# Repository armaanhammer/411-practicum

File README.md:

# 411-practicum
Development for ECE 411 Fall 2017 Group 16 Practicum

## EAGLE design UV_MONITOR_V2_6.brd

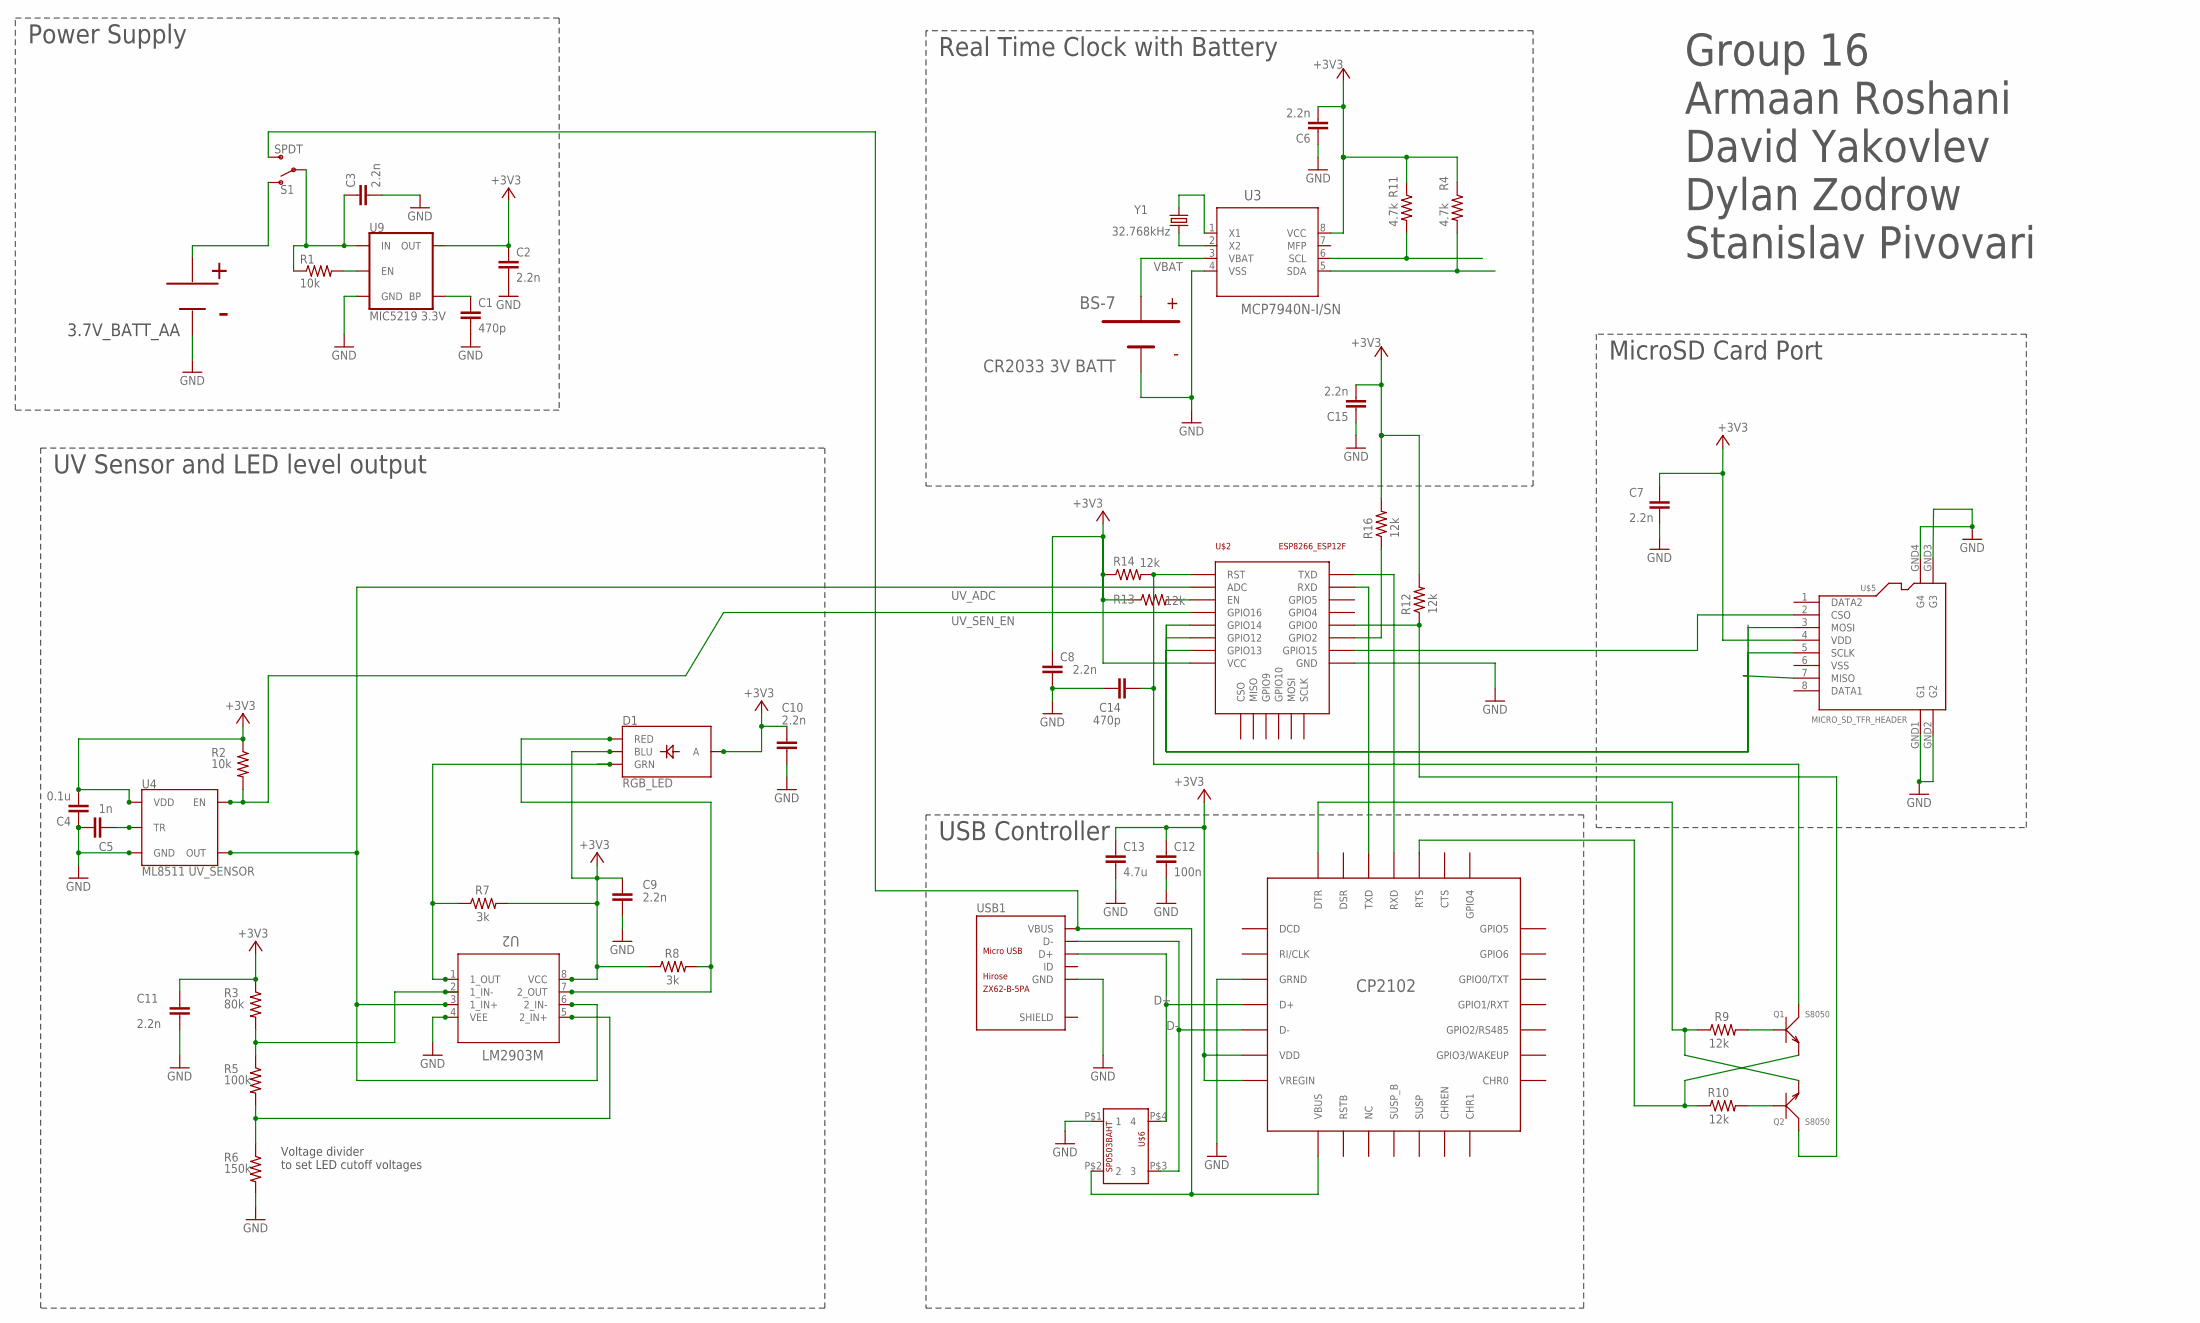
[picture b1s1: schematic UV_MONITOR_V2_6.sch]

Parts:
C1, C14: 470p; C0805
C2, C3, C6, C7, C8, C9, C10, C11, C15: 2.2n; C0805
C4: 0.1u; C0805
C5: 1n; C0805
C12: 100n; C0805
C13: 4.7u; C0805
D1: RGB_LED; LED-TRICOLOR-SMD
Q1, Q2: S8050; SOT-23
R1, R2: 10k; R0805
R3: 80k; R0805
R4, R11: 4.7k; R0805
R5: 100k; R0805
R6: 150k; R0805
R7, R8: 3k; R0805
R9, R10, R12, R13, R14, R16: 12k; R0805
S1: SPDT; SWITCH_SPST_SMD_A
U2: LM2903M; M08A
U3: MCP7940N-I/SN; SOIC8-N_MC
U4: ML8511 UV_SENSOR; ML8511
U9: MIC5219 3.3V; SOT23-5
U$1: CP2102
U$2: ESP12F
U$3: BK-53
U$4: BS-7
U$5: MICRO_SD_TFR_HEADER
U$6: SP0503BAHT
USB1: ZX62-B-5PA; MICRO-USB5+6P-SMD-0.65-AB
Y1: 32.768kHz; CRYSTAL-SMD-2X6-CYL

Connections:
+3V3: C2.1, C4.2, C6.2, C7.1, C8.1, C9.1, C10.1, C11.1, C12.1, C13.1, C15.2, D1.A, D1.B (BLU), R2.1, R3.1, R4.1, R7.2, R8.1, R11.1, R12.2, R13.1, R14.1, R16.2, U2.8 (VCC), U3.8 (VCC), U4.7 (VDD), U9.5 (OUT), U$1.VDD, U$1.VREGIN, U$2.VCC, U$5.4 (VDD)
BP: C1.1, U9.4 (BP)
D+: U$1.D+, U$6.P$4 (4), USB1.3 (D+)
D-: U$1.D-, U$6.P$3 (3), USB1.2 (D-)
EN: R1.2, U9.3 (EN)
GND: C1.2, C2.2, C3.2, C4.1, C5.2, C6.1, C7.2, C8.2, C9.2, C10.2, C11.2, C12.2, C13.2, C14.1, C15.1, R6.2, U2.4 (VEE), U3.4 (VSS), U4.5 (GND), U9.2 (GND), U$1.GND (GRND), U$1.GRND, U$2.GND, U$3.GND1, U$3.GND2, U$4.GND, U$5.GND1 (G1), U$5.GND2 (G2), U$5.GND3 (G3), U$5.GND4 (G4), U$6.P$1 (1), USB1.5 (GND)
GREEN_LED: D1.G (GRN), R7.1, U2.1 (1_OUT)
H_REF: R3.2, R5.1, U2.2 (1_IN-)
L_REF: R5.2, R6.1, U2.5 (2_IN+)
MAIN_BAT: C3.1, R1.1, S1.2, U9.1 (IN)
unnamed: Q1.1 (B), R9.2
unnamed: U3.2 (X2), Y1.X1 (1)
unnamed: Q2.1 (B), R10.2
unnamed: R13.2, U$2.EN
unnamed: U$2.GPIO12, U$5.7 (MISO)
unnamed: U3.1 (X1), Y1.X2 (2)
unnamed: U$2.GPIO15, U$5.2 (CSO)
unnamed: U$1.RXD, U$2.TXD
unnamed: U$1.TXD, U$2.RXD
unnamed: Q2.2 (E), R9.1, U$1.DTR
unnamed: C14.2, Q1.3 (C), R14.2, U$2.RST
unnamed: Q2.3 (C), R12.1, U$2.GPIO0
unnamed: R16.1, U$2.GPIO2
unnamed: U$2.GPIO13, U$5.5 (SCLK)
unnamed: U$2.GPIO14, U$5.3 (MOSI)
RED_LED: D1.R (RED), R8.2, U2.7 (2_OUT)
RTC_SCL: R11.2, U3.6 (SCL)
RTC_SDA: R4.2, U3.5 (SDA)
RTS: Q1.2 (E), R10.1, U$1.RTS
TR: C5.1, U4.10 (TR)
UV_ADC: U2.3 (1_IN+), U2.6 (2_IN-), U4.8 (OUT), U$2.ADC
UV_SEN_EN: R2.2, U4.4 (EN), U$2.GPIO16
VBAT: U3.3 (VBAT), U$4.VBAT
VBATT: S1.1 (O), U$3.VBAT1 (VBAT), U$3.VBAT2 (VBAT)
VBUS: S1.3 (S), U$1.VBUS, U$6.P$2 (2), USB1.1 (VBUS)

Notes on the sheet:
Power Supply
Real Time Clock with Battery
UV Sensor and LED level output
Voltage divider to set LED cutoff voltages
Group 16 Armaan Roshani David Yakovlev Dylan Zodrow Stanislav Pivovari
USB Controller
MicroSD Card Port

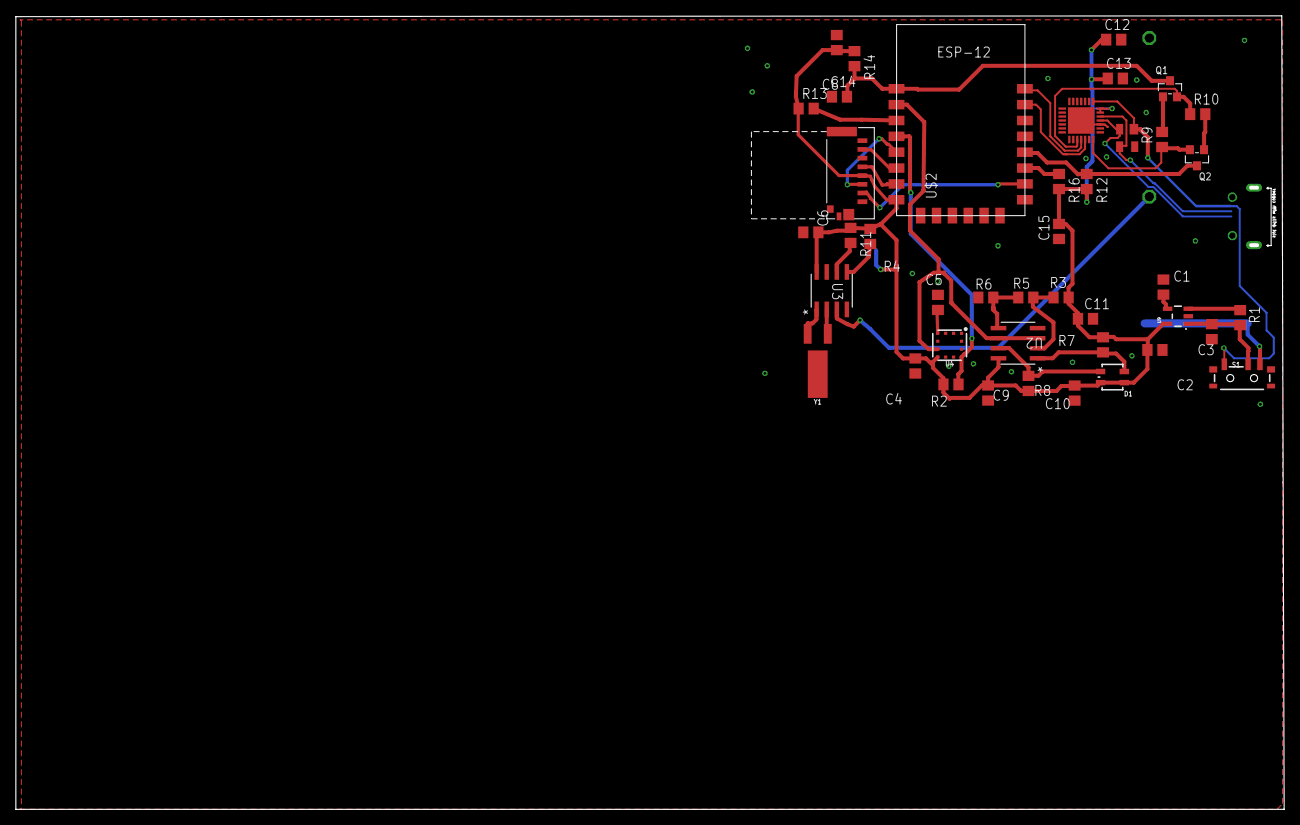
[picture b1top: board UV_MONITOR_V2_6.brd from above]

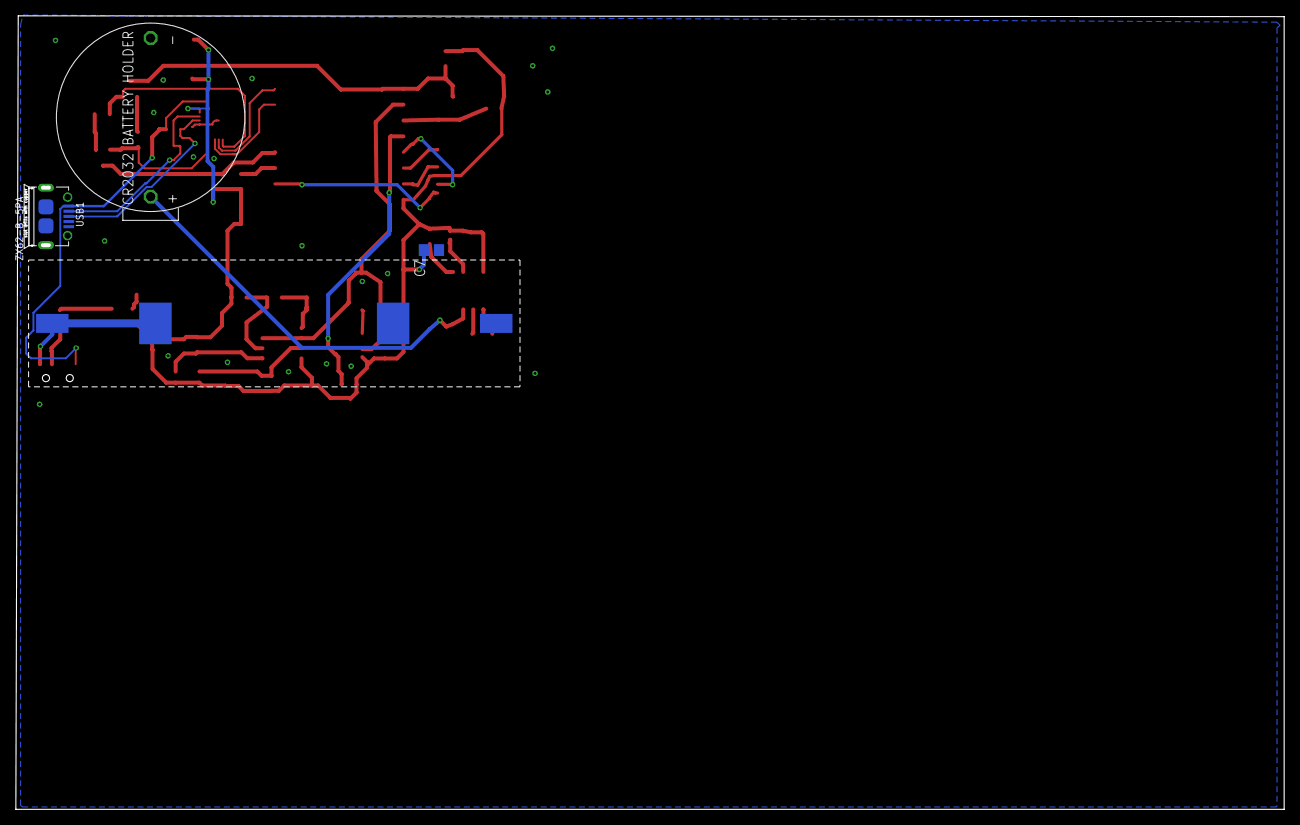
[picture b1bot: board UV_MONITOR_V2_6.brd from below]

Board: 2 copper layers, 159.5 x 99.6 mm, 46 parts (4 on the bottom side), 35 nets.

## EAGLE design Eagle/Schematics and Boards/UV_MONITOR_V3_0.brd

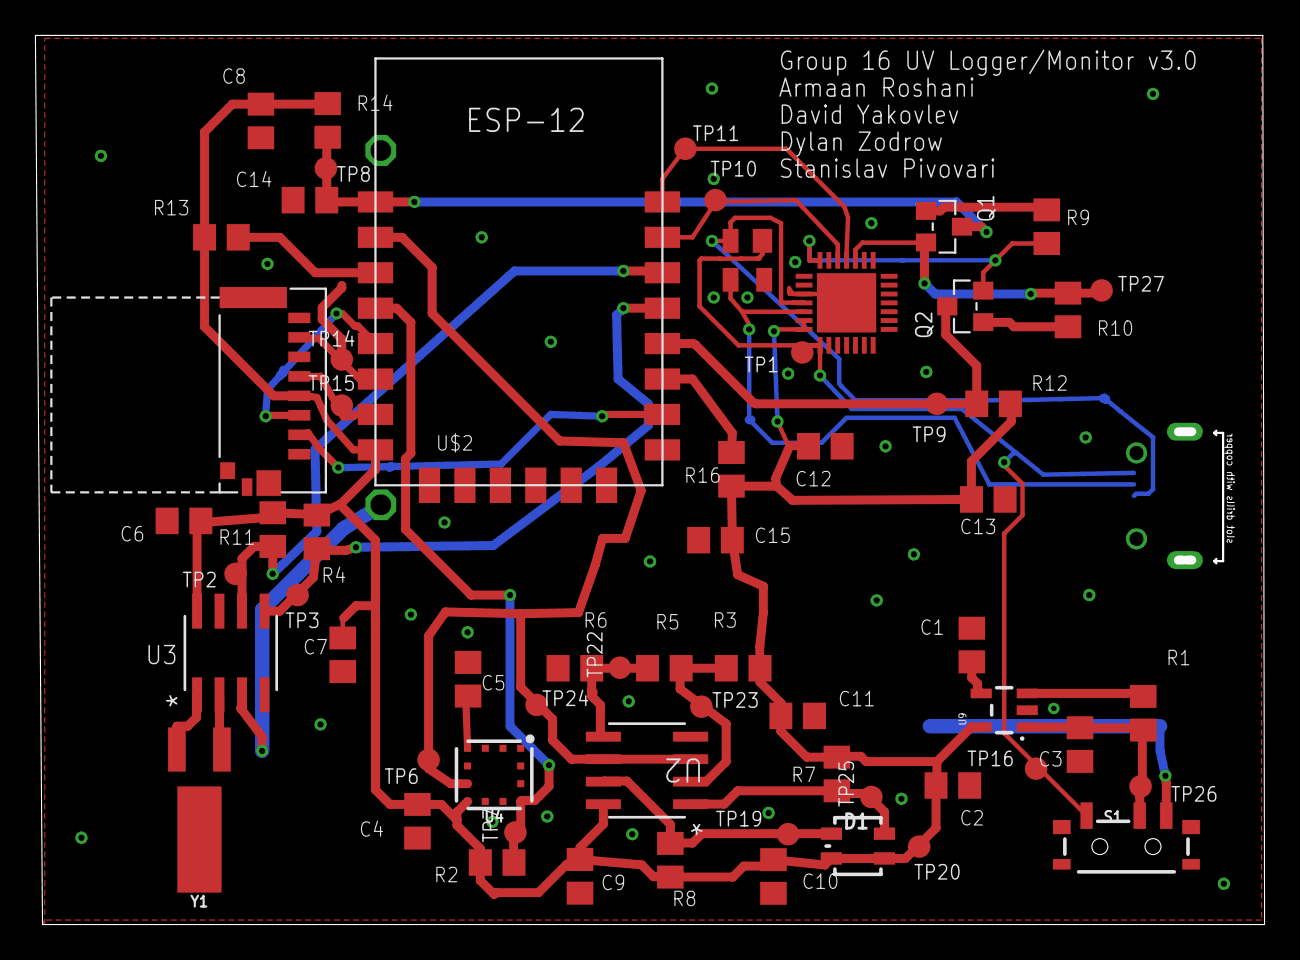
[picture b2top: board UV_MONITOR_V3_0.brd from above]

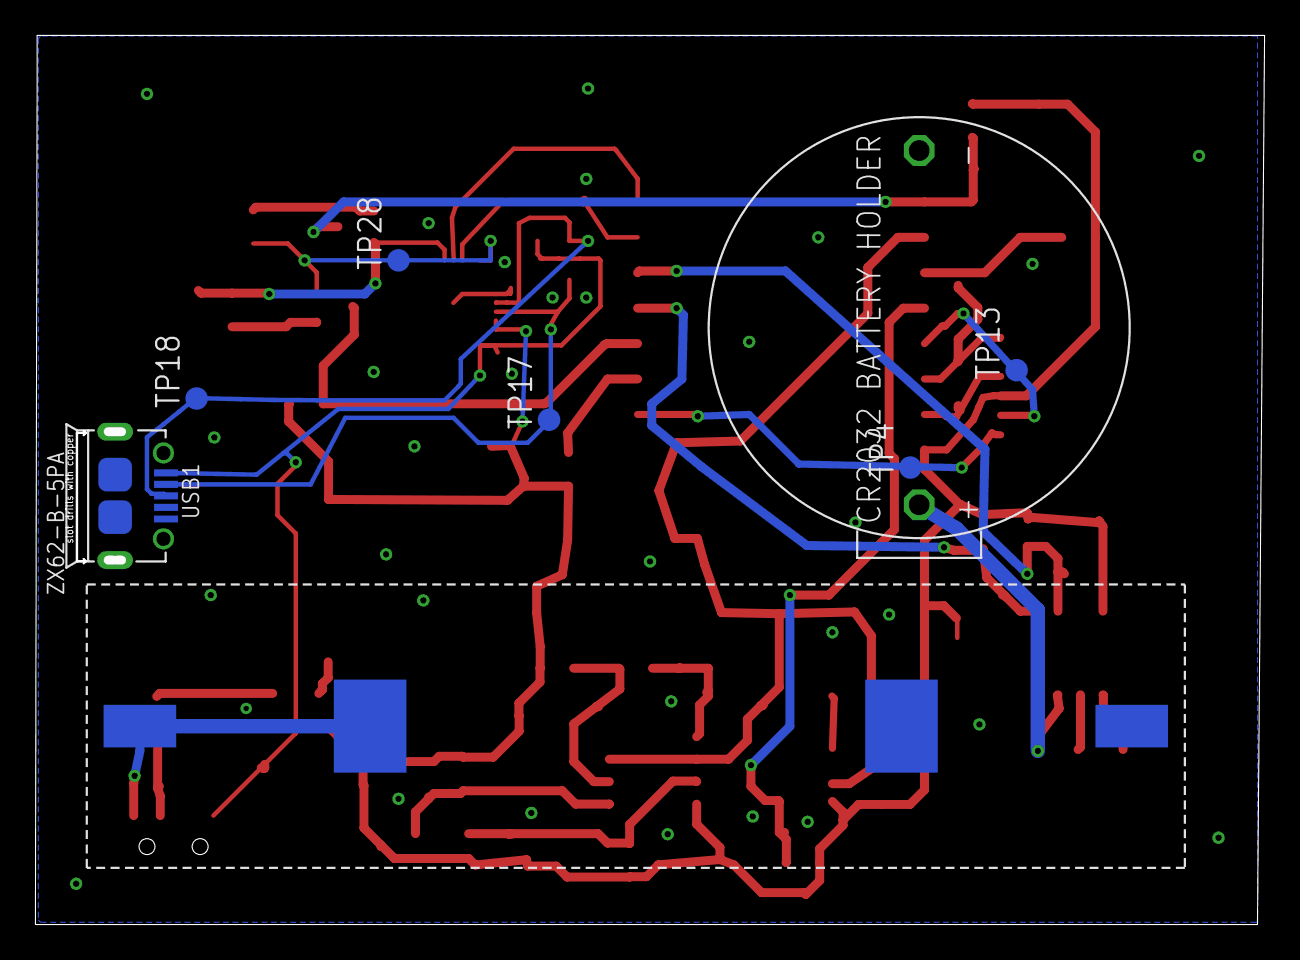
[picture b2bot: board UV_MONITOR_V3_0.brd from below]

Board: 2 copper layers, 68.9 x 49.7 mm, 71 parts (8 on the bottom side), 35 nets.

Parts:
C1, C14: 470p; C0805
C2, C3, C6, C7, C8, C9, C10, C11, C15: 2.2n; C0805
C4: 0.1u; C0805
C5: 1n; C0805
C12: 100n; C0805
C13: 4.7u; C0805
D1: RGB_LED; LED-TRICOLOR-SMD
Q1, Q2: S8050; SOT-23
R1, R2: 10k; R0805
R3: 80k; R0805
R4, R11: 4.7k; R0805
R5: 100k; R0805
R6: 150k; R0805
R7, R8: 3k; R0805
R9, R10, R12, R13, R14, R16: 12k; R0805
S1: SPDT; SWITCH_SPST_SMD_A
TP1, TP2, TP3, TP4, TP6, TP7, TP8, TP9, TP10, TP11, TP13, TP14, TP15, TP16, TP17, TP18, TP19, TP20, TP22, TP23, TP24, TP25, TP26, TP27, TP28: TPB1,27; B1,27
U2: LM2903M; M08A
U3: MCP7940N-I/SN; SOIC8-N_MC
U4: ML8511 UV_SENSOR; ML8511
U9: MIC5219 3.3V; SOT23-5
U$1: CP2102
U$2: ESP12F
U$3: BK-53
U$4: BS-7
U$5: MICRO_SD_TFR_HEADER
U$6: SP0503BAHT
USB1: ZX62-B-5PA; MICRO-USB5+6P-SMD-0.65-AB
Y1: 32.768kHz; CRYSTAL-SMD-2X6-CYL

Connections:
+3V3: C2.1, C4.2, C6.2, C7.1, C8.1, C9.1, C10.1, C11.1, C12.1, C13.1, C15.2, D1.A, D1.B, R2.1, R3.1, R4.1, R7.2, R8.1, R11.1, R12.2, R13.1, R14.1, R16.2, TP20.TP, U2.8, U3.8, U4.7, U9.5, U$1.VDD, U$1.VREGIN, U$2.VCC, U$5.4
BP: C1.1, U9.4
D+: TP18.TP, U$1.D+, U$6.P$4, USB1.3
D-: TP17.TP, U$1.D-, U$6.P$3, USB1.2
EN: R1.2, U9.3
GND: C1.2, C2.2, C3.2, C4.1, C5.2, C6.1, C7.2, C8.2, C9.2, C10.2, C11.2, C12.2, C13.2, C14.1, C15.1, R6.2, U2.4, U3.4, U4.5, U9.2, U$1.GND, U$1.GRND, U$2.GND, U$3.GND1, U$3.GND2, U$4.GND, U$5.GND1, U$5.GND2, U$5.GND3, U$5.GND4, U$6.P$1, USB1.5, USB1.P1, USB1.P2, USB1.P3, USB1.P4, USB1.P5, USB1.P6
GREEN_LED: D1.G, R7.1, TP25.TP, U2.1
H_REF: R3.2, R5.1, TP23.TP, U2.2
L_REF: R5.2, R6.1, TP22.TP, U2.5
MAIN_BAT: C3.1, R1.1, S1.2, TP26.TP, U9.1
unnamed: Q1.1, R9.2
unnamed: U3.2, Y1.X1
unnamed: Q2.1, R10.2
unnamed: R13.2, U$2.EN
unnamed: TP14.TP, U$2.GPIO12, U$5.7
unnamed: U3.1, Y1.X2
unnamed: TP4.TP, U$2.GPIO15, U$5.2
unnamed: TP11.TP, U$1.RXD, U$2.TXD
unnamed: TP10.TP, U$1.TXD, U$2.RXD
unnamed: Q2.2, R9.1, TP28.TP, U$1.DTR
unnamed: C14.2, Q1.3, R14.2, TP8.TP, U$2.RST
unnamed: Q2.3, R12.1, TP9.TP, U$2.GPIO0
unnamed: R16.1, U$2.GPIO2
unnamed: TP15.TP, U$2.GPIO13, U$5.5
unnamed: TP13.TP, U$2.GPIO14, U$5.3
RED_LED: D1.R, R8.2, TP19.TP, U2.7
RTC_SCL: R11.2, TP2.TP, U3.6, U$2.GPIO5
RTC_SDA: R4.2, TP3.TP, U3.5, U$2.GPIO4
RTS: Q1.2, R10.1, TP27.TP, U$1.RTS
TR: C5.1, U4.10
UV_ADC: TP6.TP, TP24.TP, U2.3, U2.6, U4.8, U$2.ADC
UV_SEN_EN: R2.2, TP7.TP, U4.4, U$2.GPIO16
VBAT: U3.3, U$4.VBAT
VBATT: S1.1, U$3.VBAT1, U$3.VBAT2
VBUS: S1.3, TP1.TP, TP16.TP, U$1.VBUS, U$6.P$2, USB1.1

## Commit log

2017-10-26 Add files via upload
    Ver.1 preliminary project schematic
2017-11-02 Adding our Project Schedule
    This proj sched was created using smartsheet.com and exported to XML. Soon I plan to move it over to Microsoft Project
2017-11-02 Add files via upload
    Forgot to put group # and names on previous
2017-11-09 Adding .mpp file
    Vinod requested a .mpp (Microsoft Project) file. This is the file I generated by downloading MS Project, importing the xml file, and generating a .mpp file.
2017-11-11 Code
    Code to get the UV and RTC transmitting data
2017-11-11 Library added
    Library required for RTC
2017-11-12 Working RTC
    RTC module working
2017-11-12 SDcard
    SDcard
2017-11-12 SDcard sketch debuggin
    Added a text file explaining current issues, and made minor edits to .ino files.
2017-11-14 All three devices now working.
    RTC, UV sensor, and SD Card are now working. Created a sketch called all_three.ino to test everything. It first dumps all data already in file datalog.txt and then adds a line once per second. It use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
2017-11-14 Added UV Index calc
    Included UV Index calcuation as stored value.
2017-11-14 Fixed UV Index
    changed from int to float
2017-11-15 fixing time offset
    Adding offset and modulo to minutes and seconds. This is a shitty way to fix the problem though.
2017-11-15 updated UV Index approximation and added set_RTC
    set_RTC.ino sets the time on the RTC and does nothing else. all_three.ino no longer sets the time, but does everything else. Also, UV Index is normalized and recalculated to closer approximate a reas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
2017-11-22 minor edits
    Created some edits for my own benefit. These edits were to an old version of our schematic and board.
2017-11-22 Organizing
    Moved around and renamed a lot of items. Most important change is all_three.ino has been renamed to UV_logger.ino
2017-11-22 deleting .DS_Store files
    .DS_Store is a normally hidden file that Mac OSX adds to every folder. It tracks information like icon size and placement, so is not useful at all for this repo.
2017-11-22 deleting another .DS_Store file
    .DS_Store is a normally hidden file that Mac OSX adds to every folder. It tracks information like icon size and placement, so is not useful at all for this repo.
2017-11-22 deleting a third .DS_Store file
    .DS_Store is a normally hidden file that Mac OSX adds to every folder. It tracks information like icon size and placement, so is not useful at all for this repo.
2017-11-22 deleting a fourth .DS_Store file
    .DS_Store is a normally hidden file that Mac OSX adds to every folder. It tracks information like icon size and placement, so is not useful at all for this repo.
2017-11-22 Update .gitignore
    adding .DS_Store line
2017-11-23 Create README.md
    Description of files
2017-11-23 created board and schematic archive
    moved stuff
2017-11-23 Delete .DS_Store
    omg, goaway
2017-11-23 editing polygon layers, adding PDFs

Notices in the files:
parts and their libraries:
SparkFun-LED: Licensing: Creative Commons ShareAlike 4.0 International - https://creativecommons.org/licenses/by-sa/4.0
